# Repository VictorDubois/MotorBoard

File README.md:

Custom PCB, used by KrabiV2.

Drives two brushless motors C610/M2006, controlled with dedicated encoders wheels, and 4 simple transistor outputs.

Driven by a [STM32 NUCLEO-G431KB](https://www.st.com/en/evaluation-tools/nucleo-g431kb.html)

[The code is here](https://github.com/VictorDubois/Motor-board-STM32-CAN)

[Click for online viewer<br/>

](https://kicanvas.org/?repo=https%3A%2F%2Fgithub.com%2FVictorDubois%2FMotorBoard)

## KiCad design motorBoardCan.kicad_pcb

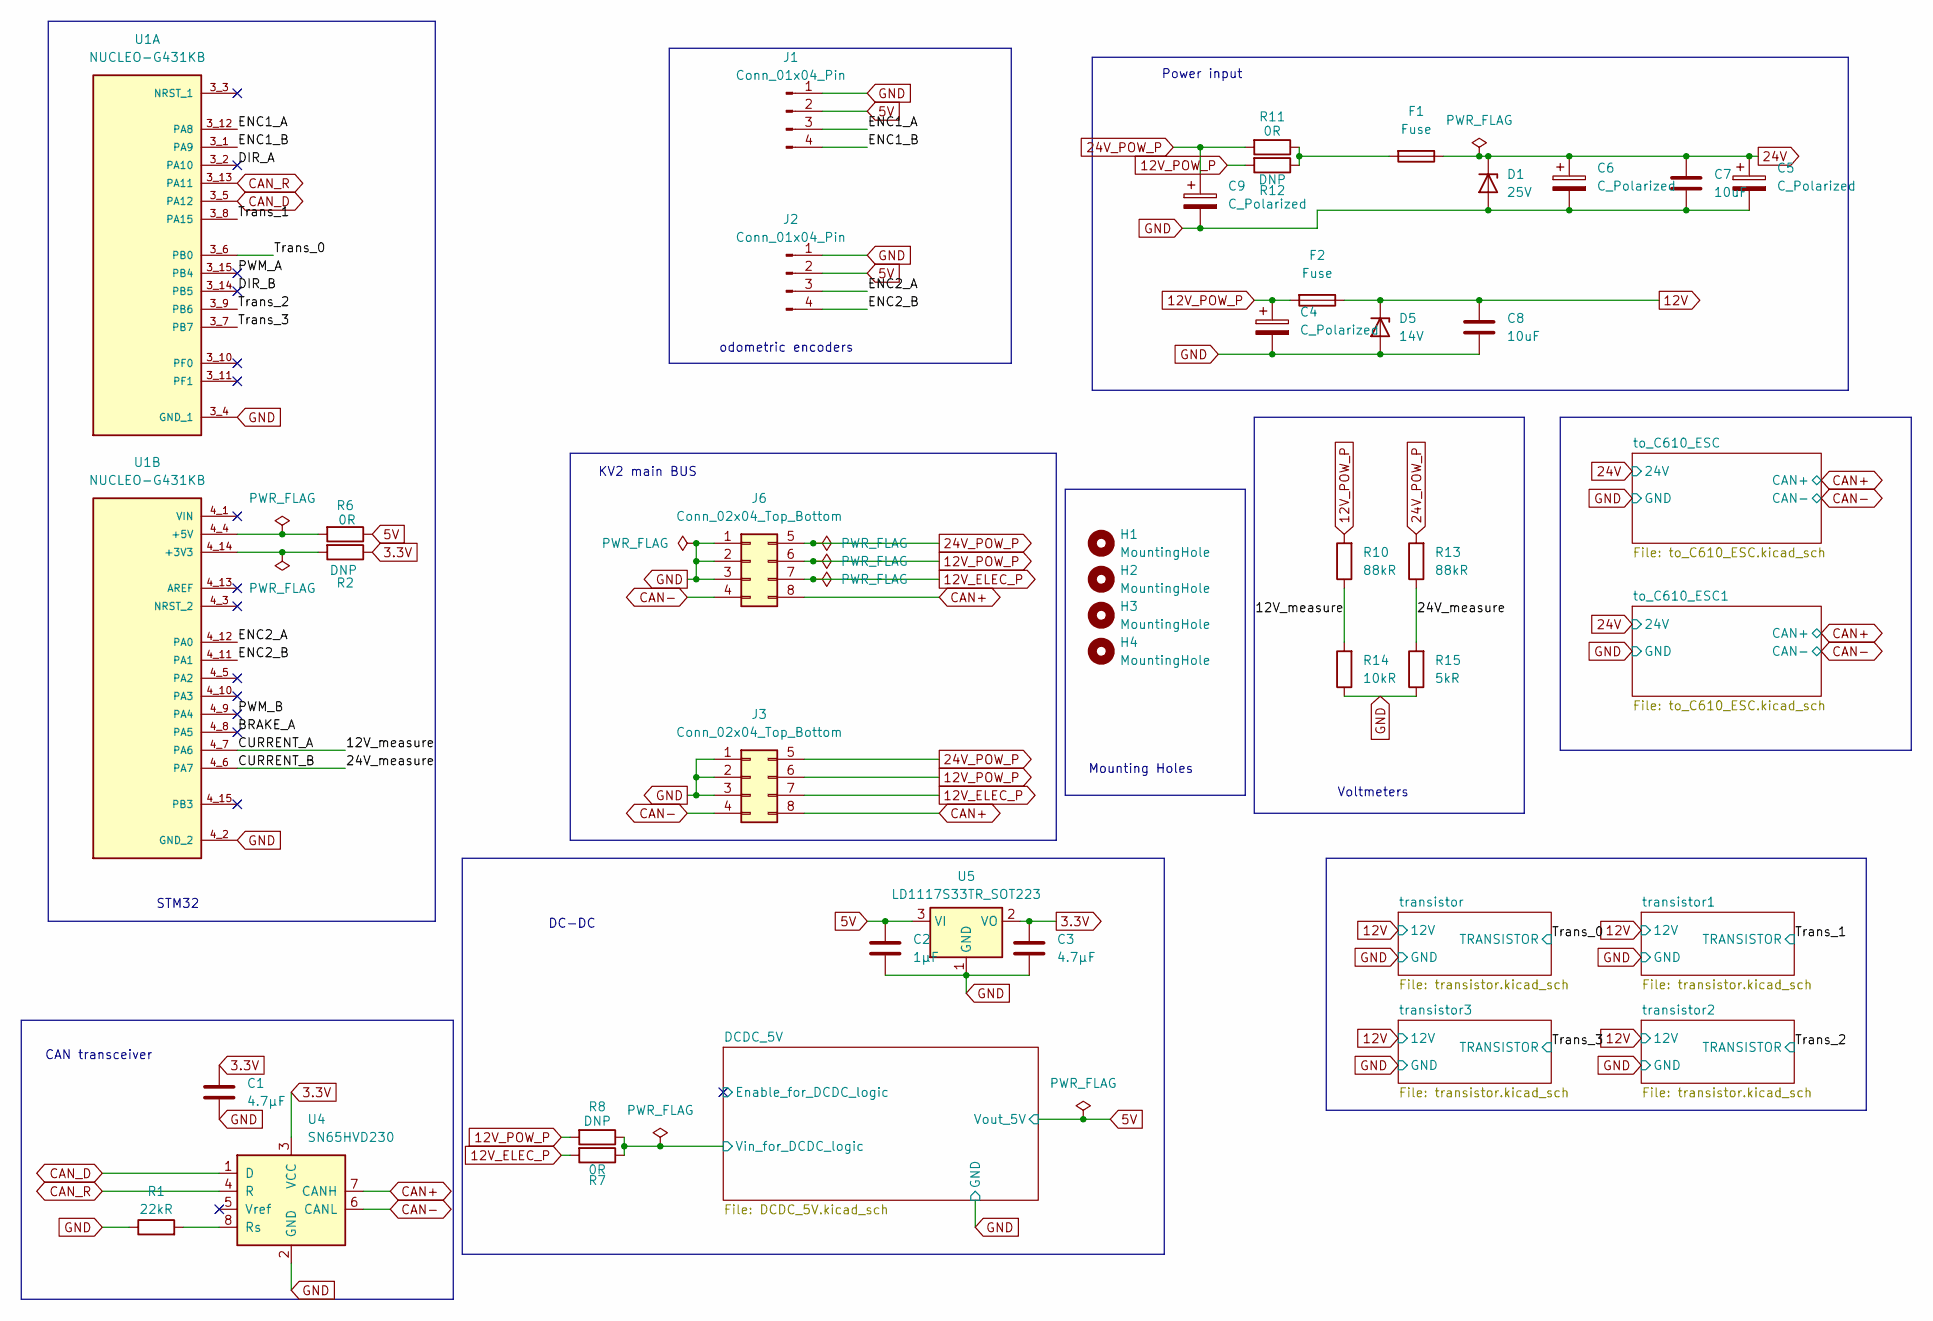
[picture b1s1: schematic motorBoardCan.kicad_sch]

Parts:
C1, C3: 4.7µF; C_1206_3216Metric; LCSC# C29823
C2: 1µF; C_1206_3216Metric; LCSC# C91151
C4, C9: C_Polarized; CP_Elec_10x10.5; LCSC# C398835
C5: C_Polarized; CP_Radial_D8.0mm_P3.50mm; LCSC# C398835
C6: C_Polarized; CP_Radial_D10.0mm_P5.00mm; LCSC# C398835
C7, C8: 10uF; C_0805_2012Metric; LCSC# C440198
D1: 25V; D_SOD-123; LCSC# C118721
D5: 14V; D_SOD-123; LCSC# C118721
F1, F2: Fuse; Fuse_Littelfuse-NANO2-451_453; LCSC# C27515
H1, H2, H3, H4: MountingHole; MountingHole_3.2mm_M3
J1, J2: Conn_01x04_Pin; JST_XH_B4B-XH-A_1x04_P2.50mm_Vertical; LCSC# C2691448
J3, J6: Conn_02x04_Top_Bottom; Molex_Micro-Fit_3.0_43045-0812_2x04_P3.00mm_Vertical; LCSC# C277661
R1: 22kR; R_0603_1608Metric; LCSC# C2907128
R2, R8: DNP; R_0603_1608Metric
R6, R7: 0R; R_0603_1608Metric; LCSC# C21189
R10, R13: 88kR; R_0603_1608Metric; LCSC# C2907128
R11: 0R; R_1206_3216Metric
R12: DNP; R_1206_3216Metric; LCSC# C21189
R14: 10kR; R_0603_1608Metric; LCSC# C2907128
R15: 5kR; R_0603_1608Metric; LCSC# C2907128
U1: NUCLEO-G431KB; MODULE_NUCLEO-G431KB
U4: SN65HVD230; SOIC-8_3.9x4.9mm_P1.27mm; LCSC# C12084
U5: LD1117S33TR_SOT223; SOT-223-3_TabPin2; LCSC# C20538890

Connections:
3.3V: C1.1, C3.1, R2.1, U4.3 (VCC), U5.2 (VO)
5V: C2.1, J1.2, J2.2, R6.1, U5.3 (VI); also elsewhere on the board
12V: C8.1, D5.1 (K), F2.1; also elsewhere on the board
12V_ELEC_P: J3.7, J6.7, R7.2
12V_POW_P: C4.1, F2.2, J3.6, J6.6, R8.2, R10.2, R12.2
24V: C5.1, C6.1, C7.1, D1.1 (K), F1.1; also elsewhere on the board
24V_POW_P: C9.1, J3.5, J6.5, R11.2, R13.2
/12V_measure: R10.1, R14.2, U1.4_7 (PA6)
/24V_measure: R13.1, R15.2, U1.4_6 (PA7)
/BRAKE_A: U1.4_8 (PA5)
/DCDC_5V/Vin_for_DCDC_logic: R7.1, R8.1; also elsewhere on the board
/DIR_A: U1.3_2 (PA10)
/DIR_B: U1.3_14 (PB5)
/ENC1_A: J1.3, U1.3_12 (PA8)
/ENC1_B: J1.4, U1.3_1 (PA9)
/ENC2_A: J2.3, U1.4_12 (PA0)
/ENC2_B: J2.4, U1.4_11 (PA1)
/PWM_A: U1.3_15 (PB4)
/PWM_B: U1.4_9 (PA4)
/Trans_0: U1.3_6 (PB0); also elsewhere on the board
/Trans_1: U1.3_8 (PA15); also elsewhere on the board
/Trans_2: U1.3_9 (PB6); also elsewhere on the board
/Trans_3: U1.3_7 (PB7); also elsewhere on the board
CAN+: J3.8, J6.8, U4.7 (CANH); also elsewhere on the board
CAN-: J3.4, J6.4, U4.6 (CANL); also elsewhere on the board
CAN_D: U1.3_5 (PA12), U4.1 (D)
CAN_R: U1.3_13 (PA11), U4.4 (R)
GND: C1.2, C2.2, C3.2, C4.2, C5.2, C6.2, C7.2, C8.2, C9.2, D1.2 (A), D5.2 (A), J1.1, J2.1, J3.1, J3.2, J3.3, J6.1, J6.2, J6.3, R1.1, R14.1, R15.1, U1.3_4 (GND_1), U1.4_2 (GND_2), U4.2 (GND), U5.1 (GND); also elsewhere on the board
unnamed: F1.2, R11.1, R12.1
unnamed: R2.2, U1.4_14 (+3V3)
unnamed: R6.2, U1.4_4 (+5V)
unnamed: R1.2, U4.8 (Rs)

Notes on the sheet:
CAN transceiver
Power input
Voltmeters
KV2 main BUS
DC-DC
Mounting Holes
STM32
odometric encoders

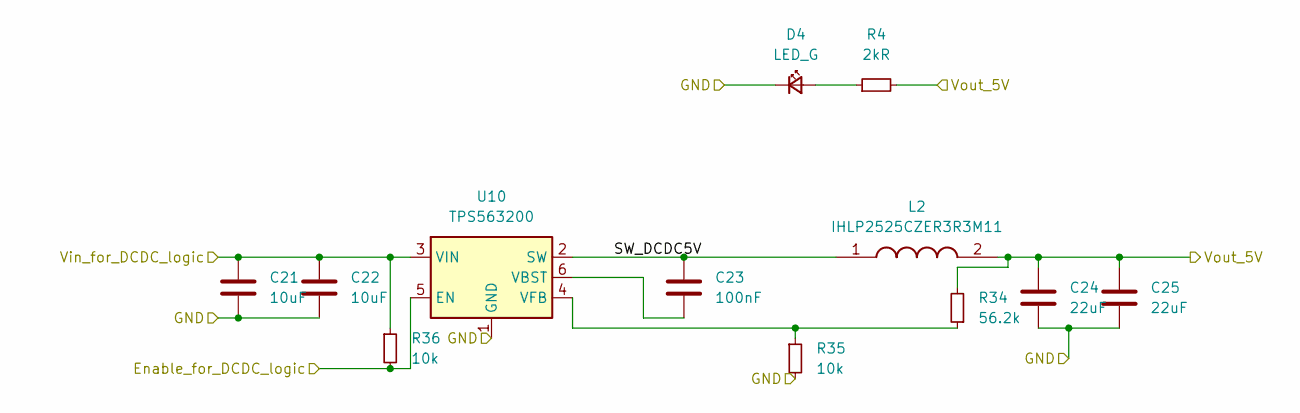
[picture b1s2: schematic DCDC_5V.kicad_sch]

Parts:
C21, C22: 10uF; C_0805_2012Metric; LCSC# C440198
C23: 100nF; C_0603_1608Metric; LCSC# C14663
C24, C25: 22uF; C_0805_2012Metric; LCSC# C29277
D4: LED_G; LED_0805_2012Metric; LCSC# C965815
L2: IHLP2525CZER3R3M11; INDPM6965X300N; Mouser Part Number 70-IHLP2525CZER3R3M1
R4: 2kR; R_0603_1608Metric; LCSC# C2907137
R34: 56.2k; C_0603_1608Metric; LCSC# C2930117
R35, R36: 10k; C_0603_1608Metric; LCSC# C2930027
U10: TPS563200; SOT-23-6; LCSC# C97253

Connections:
5V: C24.1, C25.1, L2.2, R4.2, R34.2; also elsewhere on the board
/DCDC_5V/Enable_for_DCDC_logic: R36.2, U10.5 (EN)
/DCDC_5V/SW_DCDC5V: C23.1, L2.1, U10.2 (SW)
/DCDC_5V/Vin_for_DCDC_logic: C21.1, C22.1, R36.1, U10.3 (VIN); also elsewhere on the board
GND: C21.2, C22.2, C24.2, C25.2, D4.1 (K), R35.2, U10.1 (GND); also elsewhere on the board
unnamed: D4.2 (A), R4.1
unnamed: C23.2, U10.6 (VBST)
unnamed: R34.1, R35.1, U10.4 (VFB)

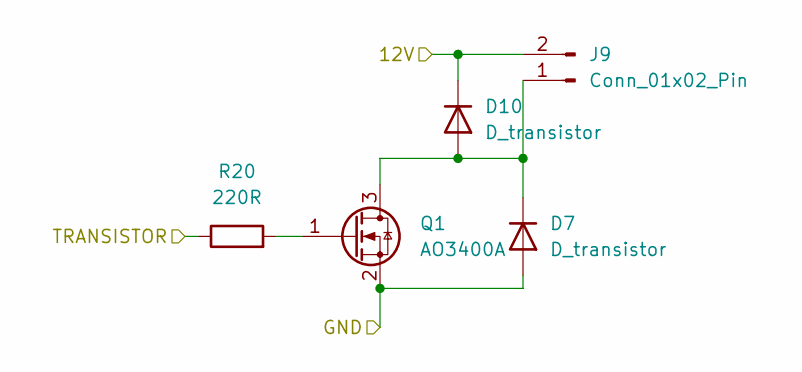
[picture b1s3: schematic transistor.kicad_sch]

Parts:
D7, D10: D_transistor; D_SOD-123; LCSC# C908230
J9: Conn_01x02_Pin; JST_XH_B2B-XH-A_1x02_P2.50mm_Vertical; LCSC# C158012
Q1: AO3400A; SOT-23; LCSC# C20917
R20: 220R; R_0603_1608Metric; LCSC# C2907127

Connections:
12V: D10.1 (K), J9.2; also elsewhere on the board
/Trans_0: R20.1; also elsewhere on the board
GND: D7.2 (A), Q1.2 (S); also elsewhere on the board
unnamed: D7.1 (K), D10.2 (A), J9.1, Q1.3 (D)
unnamed: Q1.1 (G), R20.2

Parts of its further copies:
D6, D8, D9, D11, D12, D13: D_transistor; D_SOD-123; LCSC# C908230
J10, J11, J12: Conn_01x02_Pin; JST_XH_B2B-XH-A_1x02_P2.50mm_Vertical; LCSC# C158012
Q2, Q3, Q4: AO3400A; SOT-23; LCSC# C20917
R3, R5, R9: 220R; R_0603_1608Metric; LCSC# C2907127

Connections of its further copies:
12V: D11.1 (K), D12.1 (K), D13.1 (K), J10.2, J11.2, J12.2; also elsewhere on the board
/Trans_1: R3.1; also elsewhere on the board
/Trans_2: R5.1; also elsewhere on the board
/Trans_3: R9.1; also elsewhere on the board
GND: D6.2 (A), D8.2 (A), D9.2 (A), Q2.2 (S), Q3.2 (S), Q4.2 (S); also elsewhere on the board
unnamed: D6.1 (K), D11.2 (A), J10.1, Q2.3 (D)
unnamed: D8.1 (K), D12.2 (A), J11.1, Q3.3 (D)
unnamed: D9.1 (K), D13.2 (A), J12.1, Q4.3 (D)
unnamed: Q2.1 (G), R3.2
unnamed: Q3.1 (G), R5.2
unnamed: Q4.1 (G), R9.2

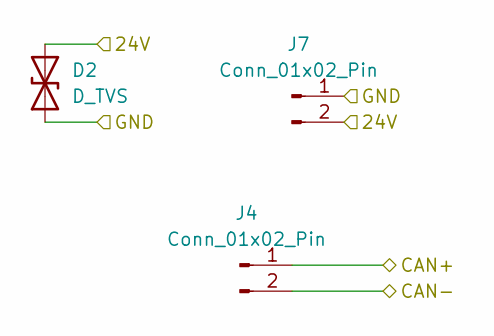
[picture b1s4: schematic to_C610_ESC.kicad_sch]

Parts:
D2: D_TVS; D_SMA; LCSC# C908774
J4: Conn_01x02_Pin; JST_XH_B2B-XH-A_1x02_P2.50mm_Vertical; LCSC# C158012
J7: Conn_01x02_Pin; AMASS_XT30UPB-F_1x02_P5.0mm_Vertical; LCSC# C108769

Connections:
24V: D2.2 (A2), J7.2; also elsewhere on the board
CAN+: J4.1; also elsewhere on the board
CAN-: J4.2; also elsewhere on the board
GND: D2.1 (A1), J7.1; also elsewhere on the board

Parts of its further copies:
D3: D_TVS; D_SMA; LCSC# C908774
J5: Conn_01x02_Pin; JST_XH_B2B-XH-A_1x02_P2.50mm_Vertical; LCSC# C158012
J8: Conn_01x02_Pin; AMASS_XT30UPB-F_1x02_P5.0mm_Vertical; LCSC# C108769

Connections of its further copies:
24V: D3.2 (A2), J8.2; also elsewhere on the board
CAN+: J5.1; also elsewhere on the board
CAN-: J5.2; also elsewhere on the board
GND: D3.1 (A1), J8.1; also elsewhere on the board

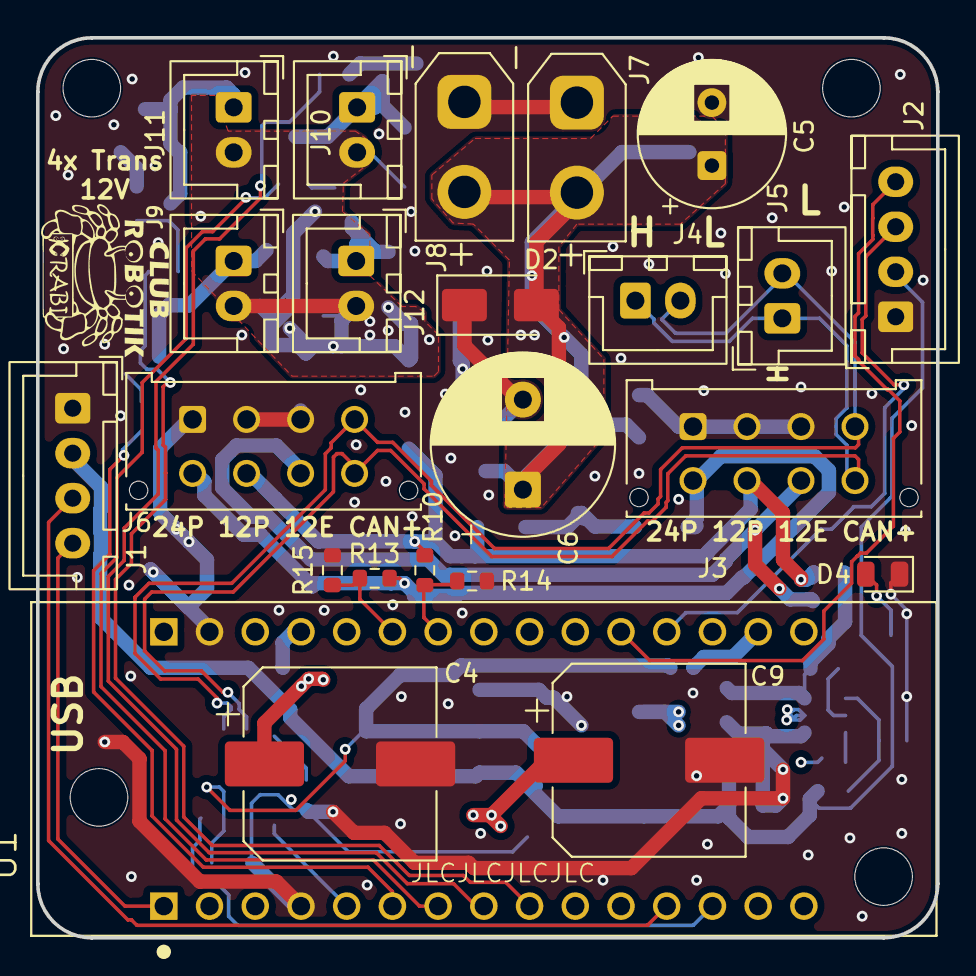
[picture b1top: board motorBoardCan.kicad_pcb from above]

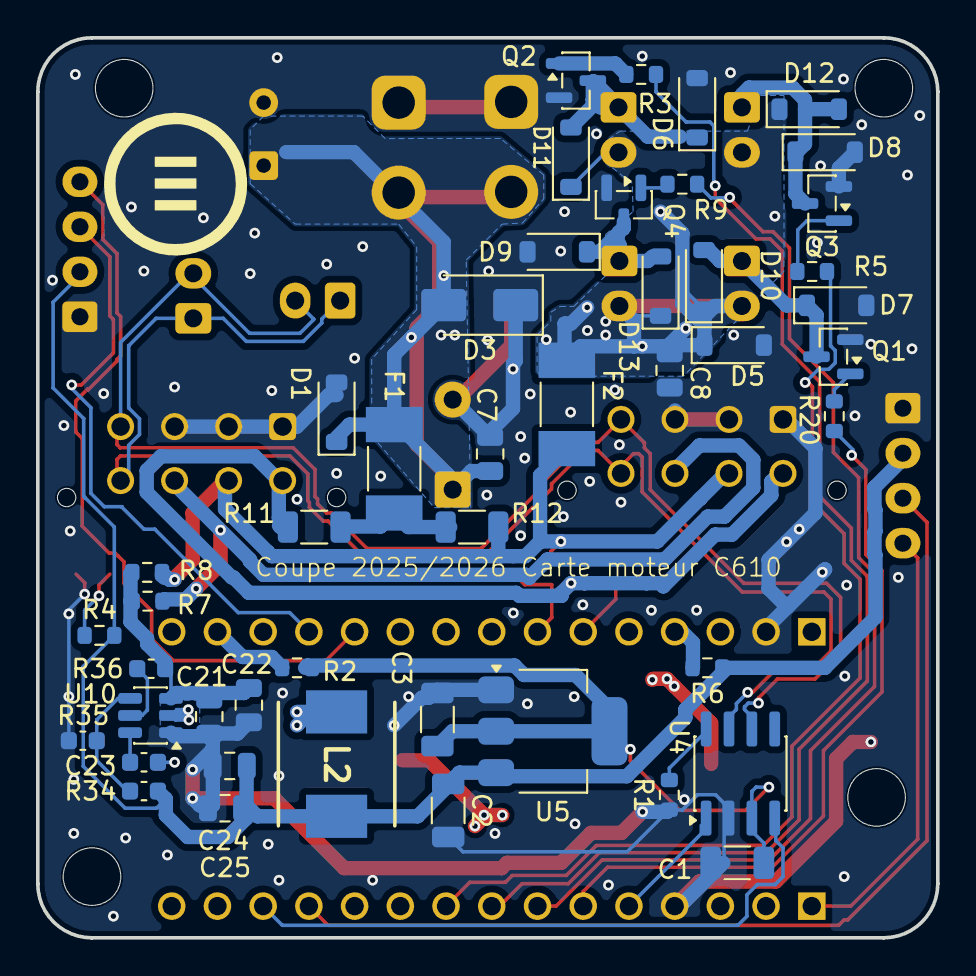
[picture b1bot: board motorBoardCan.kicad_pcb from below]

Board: 6 copper layers, 50.0 x 50.0 mm, 73 parts (46 on the bottom side), 40 nets.

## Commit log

2018-03-22 close #1 creation
2022-08-28 second board version
2022-10-08 add readme
2025-08-15 Add option 12V Elec + add missing brake pullups
2025-08-15 add choice between 12V power and 24V power
2026-01-18 remove DC motors + schematic labels
2026-01-18 basic routing of C610 connectors
2026-01-18 small tuning
2026-01-18 serigraphy
2026-01-21 move capacitors for easier access to main bus connectors + add 24V flood fill
2026-02-05 various updates
2026-02-05 remove pressure measure, add voltage measure, re-route
2026-02-06 change capacitor references to support >25V
2026-05-21 Initialize README with project details and links
    Added project description and links for motor board control.
2026-06-20 fix transistor by adding a correct free-wheeling diode
2026-06-20 update to Kicad 10 + fix warnings
2026-06-20 bigger jumper resistors
2026-06-20 improve GND routing
2026-06-20 Clarify PCB usage for Krabi V1 and V2
    Updated README to specify Krabi V1 and V2 PCB usage.
2026-06-20 fix readme
